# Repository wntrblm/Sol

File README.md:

# Winterbloom Sol

Winterbloom Sol is an open-source Eurorack module. You can find out more at https://wntr.dev/sol.

## License and contributing

The code here is available under the [MIT License](firmware/LICENSE), the hardware designs are available under [CC-BY-SA 4.0](hardware/LICENSE). I welcome contributors, please read the [Code of Conduct](CODE_OF_CONDUCT.md) first. :)

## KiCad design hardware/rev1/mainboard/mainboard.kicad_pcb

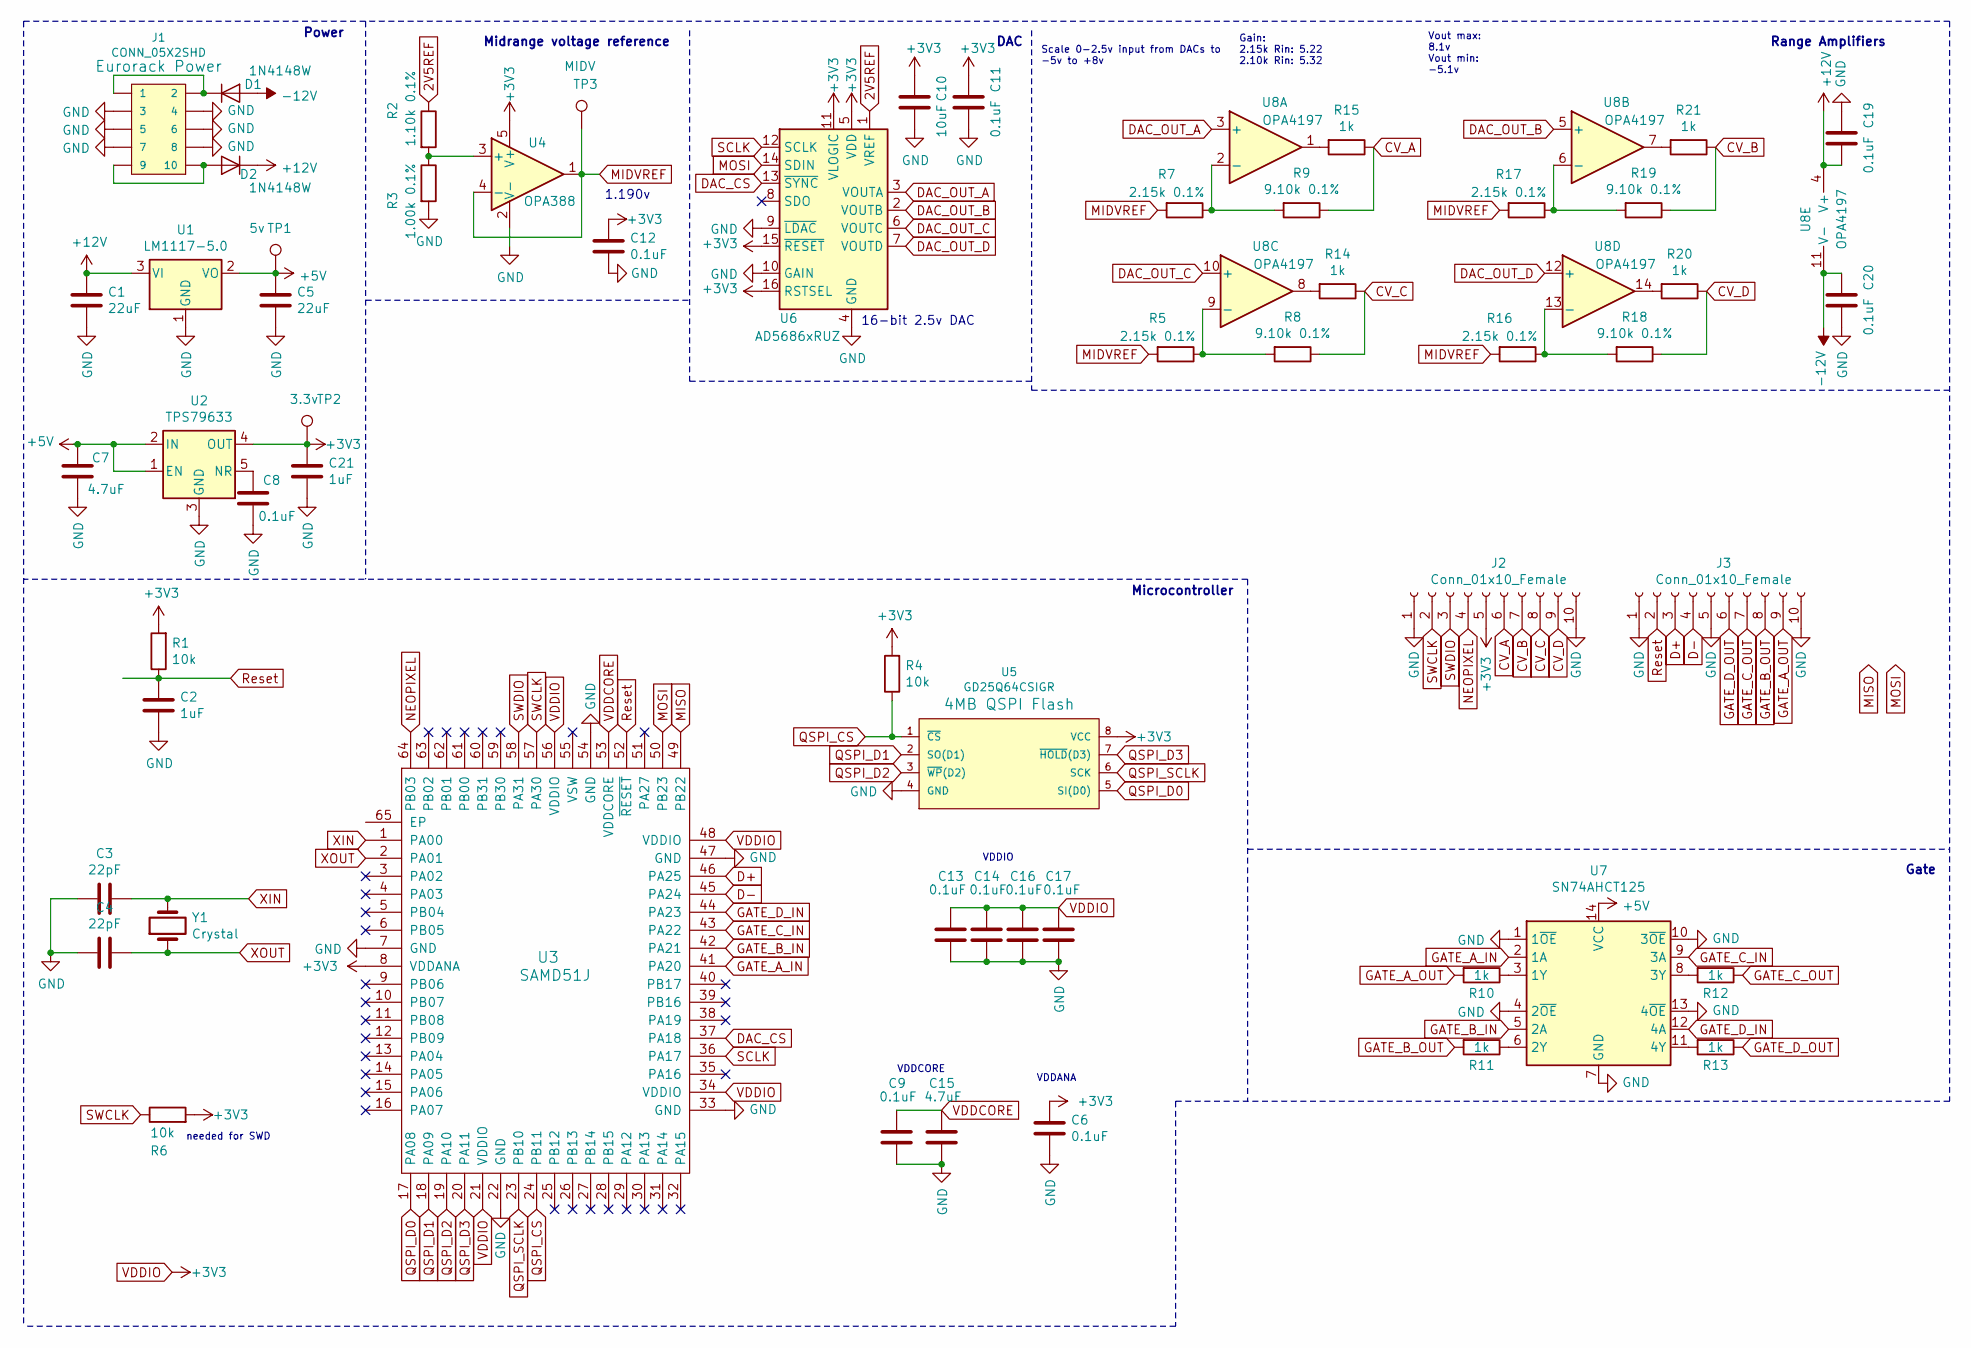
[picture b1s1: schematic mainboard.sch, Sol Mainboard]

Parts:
C1, C5: 22uF; C_0805_2012Metric_Pad1.15x1.40mm_HandSolder; mpn GRM21BR61E226ME44L
C2, C21: 1uF; C_0603_1608Metric_Pad1.05x0.95mm_HandSolder; mpn MF-CAP-0603-1uF
C3, C4: 22pF; C_0603_1608Metric_Pad1.05x0.95mm_HandSolder; mpn MF-CAP-0603-22pF
C6, C8, C9, C11, C12, C13, C14, C16, C17, C19, C20: 0.1uF; C_0603_1608Metric_Pad1.05x0.95mm_HandSolder; mpn MF-CAP-0603-0.1uF
C7, C15: 4.7uF; C_0805_2012Metric_Pad1.15x1.40mm_HandSolder; mpn GRM21BZ71E475KE15L
C10: 10uF; C_1206_3216Metric_Pad1.42x1.75mm_HandSolder; mpn MF-CAP-1206-10uF
D1, D2: 1N4148W; D_SOD-123; mpn MF-DIO-SOD123-1N4148
J1: CONN_05X2SHD; 2X5-SHROUDED; mpn 61201021621
J2, J3: Conn_01x10_Female; 1X10; mpn MF-CON-2.54mm-01x10
R1, R4, R6: 10k; R_0805_2012Metric_Pad1.15x1.40mm_HandSolder; mpn MF-RES-0805-10K
R2: 1.10k 0.1%; R_1206_3216Metric_Pad1.42x1.75mm_HandSolder; mpn ERA-8AEB112V
R3: 1.00k 0.1%; R_1206_3216Metric_Pad1.42x1.75mm_HandSolder; mpn ERA8AEB102V
R5, R7, R16, R17: 2.15k 0.1%; R_1206_3216Metric_Pad1.42x1.75mm_HandSolder; mpn ERA-8AEB2151V
R8, R9, R18, R19: 9.10k 0.1%; R_1206_3216Metric_Pad1.42x1.75mm_HandSolder; mpn ERA8AEB912V
R10, R11, R12, R13, R14, R15, R20, R21: 1k; R_0805_2012Metric_Pad1.15x1.40mm_HandSolder; mpn MF-RES-0805-1K
TP1: 5v; TestPoint_THTPad_D1.5mm_Drill0.7mm
TP2: 3.3v; TestPoint_THTPad_D1.5mm_Drill0.7mm
TP3: MIDV; TestPoint_THTPad_D1.5mm_Drill0.7mm
U1: LM1117-5.0; SOT-223-3_TabPin2; mpn LM1117IMPX-5.0/NOPB
U2: TPS79633; SOT-223-6_TabPin3; mpn TPS79633DCQR
U3: SAMD51J; TQFP-64_10x10mm_P0.5mm; mpn ATSAMD51J20A-AUT
U4: OPA388; TSOT-23-5_HandSoldering; mpn OPA388IDBVT
U5: GD25Q64CSIGR; SOIC-8; mpn GD25Q64CSIGR
U6: AD5686xRUZ; TSSOP-16_4.4x5mm_P0.65mm; mpn AD5686RBRUZ
U7: SN74AHCT125; TSSOP-14_4.4x5mm_P0.65mm; mpn SN74AHCT125QPWRQ1
U8: OPA4197; TSSOP-14_4.4x5mm_P0.65mm; mpn OPA4197IPWR
Y1: Crystal; Crystal_SMD_2012-2Pin_2.0x1.2mm_HandSoldering; mpn ABS06-32.768KHZ-1-T

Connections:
2V5REF: R2.1, U6.1 (VREF)
+5V: C5.1, C7.1, TP1.1, U1.2 (VO), U2.1 (EN), U2.2 (IN), U7.14 (VCC)
+12V: C1.1, C19.1, D2.1 (K), U1.3 (VI), U8.4 (V+)
-12V: C20.2, D1.2 (A), U8.11 (V-)
CV_A: J2.6, R9.1, R15.1
CV_B: J2.7, R19.1, R21.1
CV_C: J2.8, R8.1, R14.1
CV_D: J2.9, R18.1, R20.1
D+: J3.3, U3.46 (PA25)
D-: J3.4, U3.45 (PA24)
DAC_CS: U3.37 (PA18), U6.13 (~SYNC)
DAC_OUT_A: U6.3 (VOUTA), U8.3 (+)
DAC_OUT_B: U6.2 (VOUTB), U8.5 (+)
DAC_OUT_C: U6.6 (VOUTC), U8.10 (+)
DAC_OUT_D: U6.7 (VOUTD), U8.12 (+)
GATE_A_IN: U3.41 (PA20), U7.2 (1A)
GATE_A_OUT: J3.9, R10.2
GATE_B_IN: U3.42 (PA21), U7.5 (2A)
GATE_B_OUT: J3.8, R11.2
GATE_C_IN: U3.43 (PA22), U7.9 (3A)
GATE_C_OUT: J3.7, R12.1
GATE_D_IN: U3.44 (PA23), U7.12 (4A)
GATE_D_OUT: J3.6, R13.1
GND: C1.2, C2.2, C3.2, C4.2, C5.2, C6.2, C7.2, C8.2, C9.2, C10.2, C11.2, C12.1, C13.2, C14.2, C15.2, C16.2, C17.1, C19.2, C20.1, C21.2, J1.3, J1.4, J1.5, J1.6, J1.7, J1.8, J2.1, J2.10, J3.1, J3.5, J3.10, R3.2, U1.1 (GND), U2.3 (GND), U3.7 (GND), U3.22 (GND), U3.33 (GND), U3.47 (GND), U3.54 (GND), U4.2 (V-), U5.4 (GND), U6.4 (GND), U6.9 (~LDAC), U6.10 (GAIN), U7.1 (1~OE), U7.4 (2~OE), U7.7 (GND), U7.10 (3~OE), U7.13 (4~OE)
MIDVREF: R5.2, R7.2, R16.2, R17.2, TP3.1, U4.1, U4.4 (-)
MISO: U3.49 (PB22)
MOSI: U3.50 (PB23), U6.14 (SDIN)
NEOPIXEL: J2.4, U3.64 (PB03)
unnamed: C8.1, U2.5 (NR)
unnamed: D1.1 (K), J1.1, J1.2
unnamed: D2.2 (A), J1.9, J1.10
unnamed: R2.2, R3.1, U4.3 (+)
unnamed: R5.1, R8.2, U8.9 (-)
unnamed: R7.1, R9.2, U8.2 (-)
unnamed: R10.1, U7.3 (1Y)
unnamed: R11.1, U7.6 (2Y)
unnamed: R12.2, U7.8 (3Y)
unnamed: R13.2, U7.11 (4Y)
unnamed: R14.2, U8.8
unnamed: R15.2, U8.1
unnamed: R16.1, R18.2, U8.13 (-)
unnamed: R17.1, R19.2, U8.6 (-)
unnamed: R20.2, U8.14
unnamed: R21.2, U8.7
QSPI_CS: R4.1, U3.24 (PB11), U5.1 (~CS~)
QSPI_D0: U3.17 (PA08), U5.5 (SI(D0))
QSPI_D1: U3.18 (PA09), U5.2 (SO(D1))
QSPI_D2: U3.19 (PA10), U5.3 (~WP~(D2))
QSPI_D3: U3.20 (PA11), U5.7 (~HOLD~(D3))
QSPI_SCLK: U3.23 (PB10), U5.6 (SCK)
Reset: C2.1, J3.2, R1.1, U3.52 (~RESET)
SCLK: U3.36 (PA17), U6.12 (SCLK)
SWCLK: J2.2, R6.1, U3.57 (PA30)
SWDIO: J2.3, U3.58 (PA31)
VDDCORE: C9.1, C15.1, U3.53 (VDDCORE)
VDDIO: C6.1, C10.1, C11.1, C12.2, C13.1, C14.1, C16.1, C17.2, C21.1, J2.5, R1.2, R4.2, R6.2, TP2.1, U2.4 (OUT), U3.8 (VDDANA), U3.21 (VDDIO), U3.34 (VDDIO), U3.48 (VDDIO), U3.56 (VDDIO), U4.5 (V+), U5.8 (VCC), U6.5 (VDD), U6.11 (VLOGIC), U6.15 (~RESET), U6.16 (RSTSEL)
XIN: C3.1, U3.1 (PA00), Y1.2
XOUT: C4.1, U3.2 (PA01), Y1.1

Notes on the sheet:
Power
Microcontroller
16-bit 2.5v DAC
Midrange voltage reference
1.190v
DAC
Gate
Scale 0-2.5v input from DACs to -5v to +8v
Range Amplifiers
Gain: 2.15k Rin: 5.22 2.10k Rin: 5.32
Vout max: 8.1v Vout min: -5.1v
needed for SWD
VDDIO
VDDCORE
VDDANA

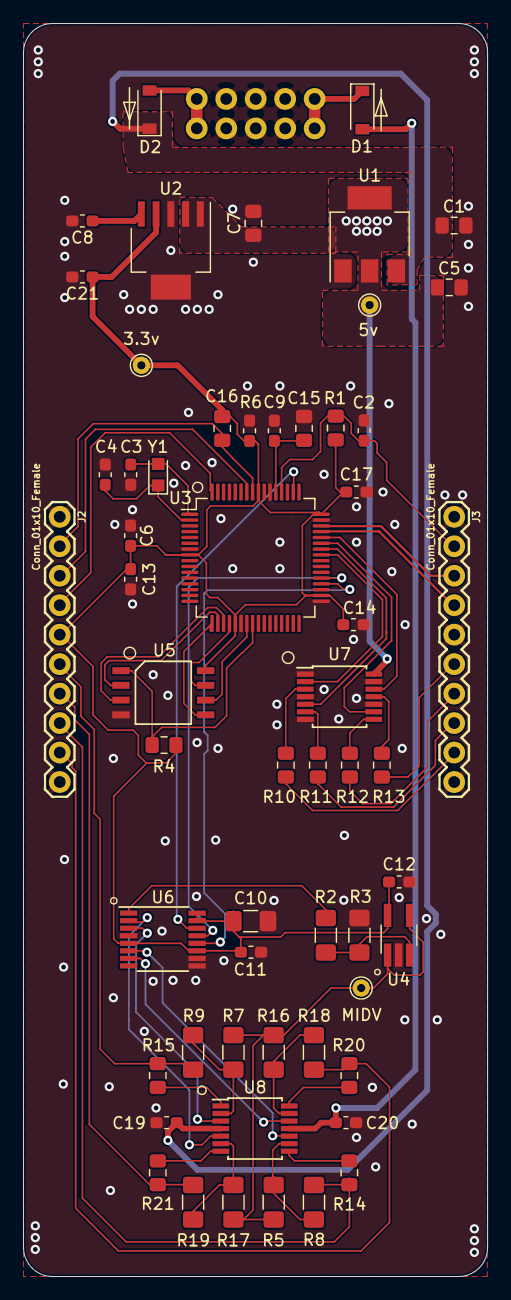
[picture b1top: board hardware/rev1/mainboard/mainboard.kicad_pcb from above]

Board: 2 copper layers, 40.0 x 108.0 mm, 58 parts (1 on the bottom side), 57 nets.

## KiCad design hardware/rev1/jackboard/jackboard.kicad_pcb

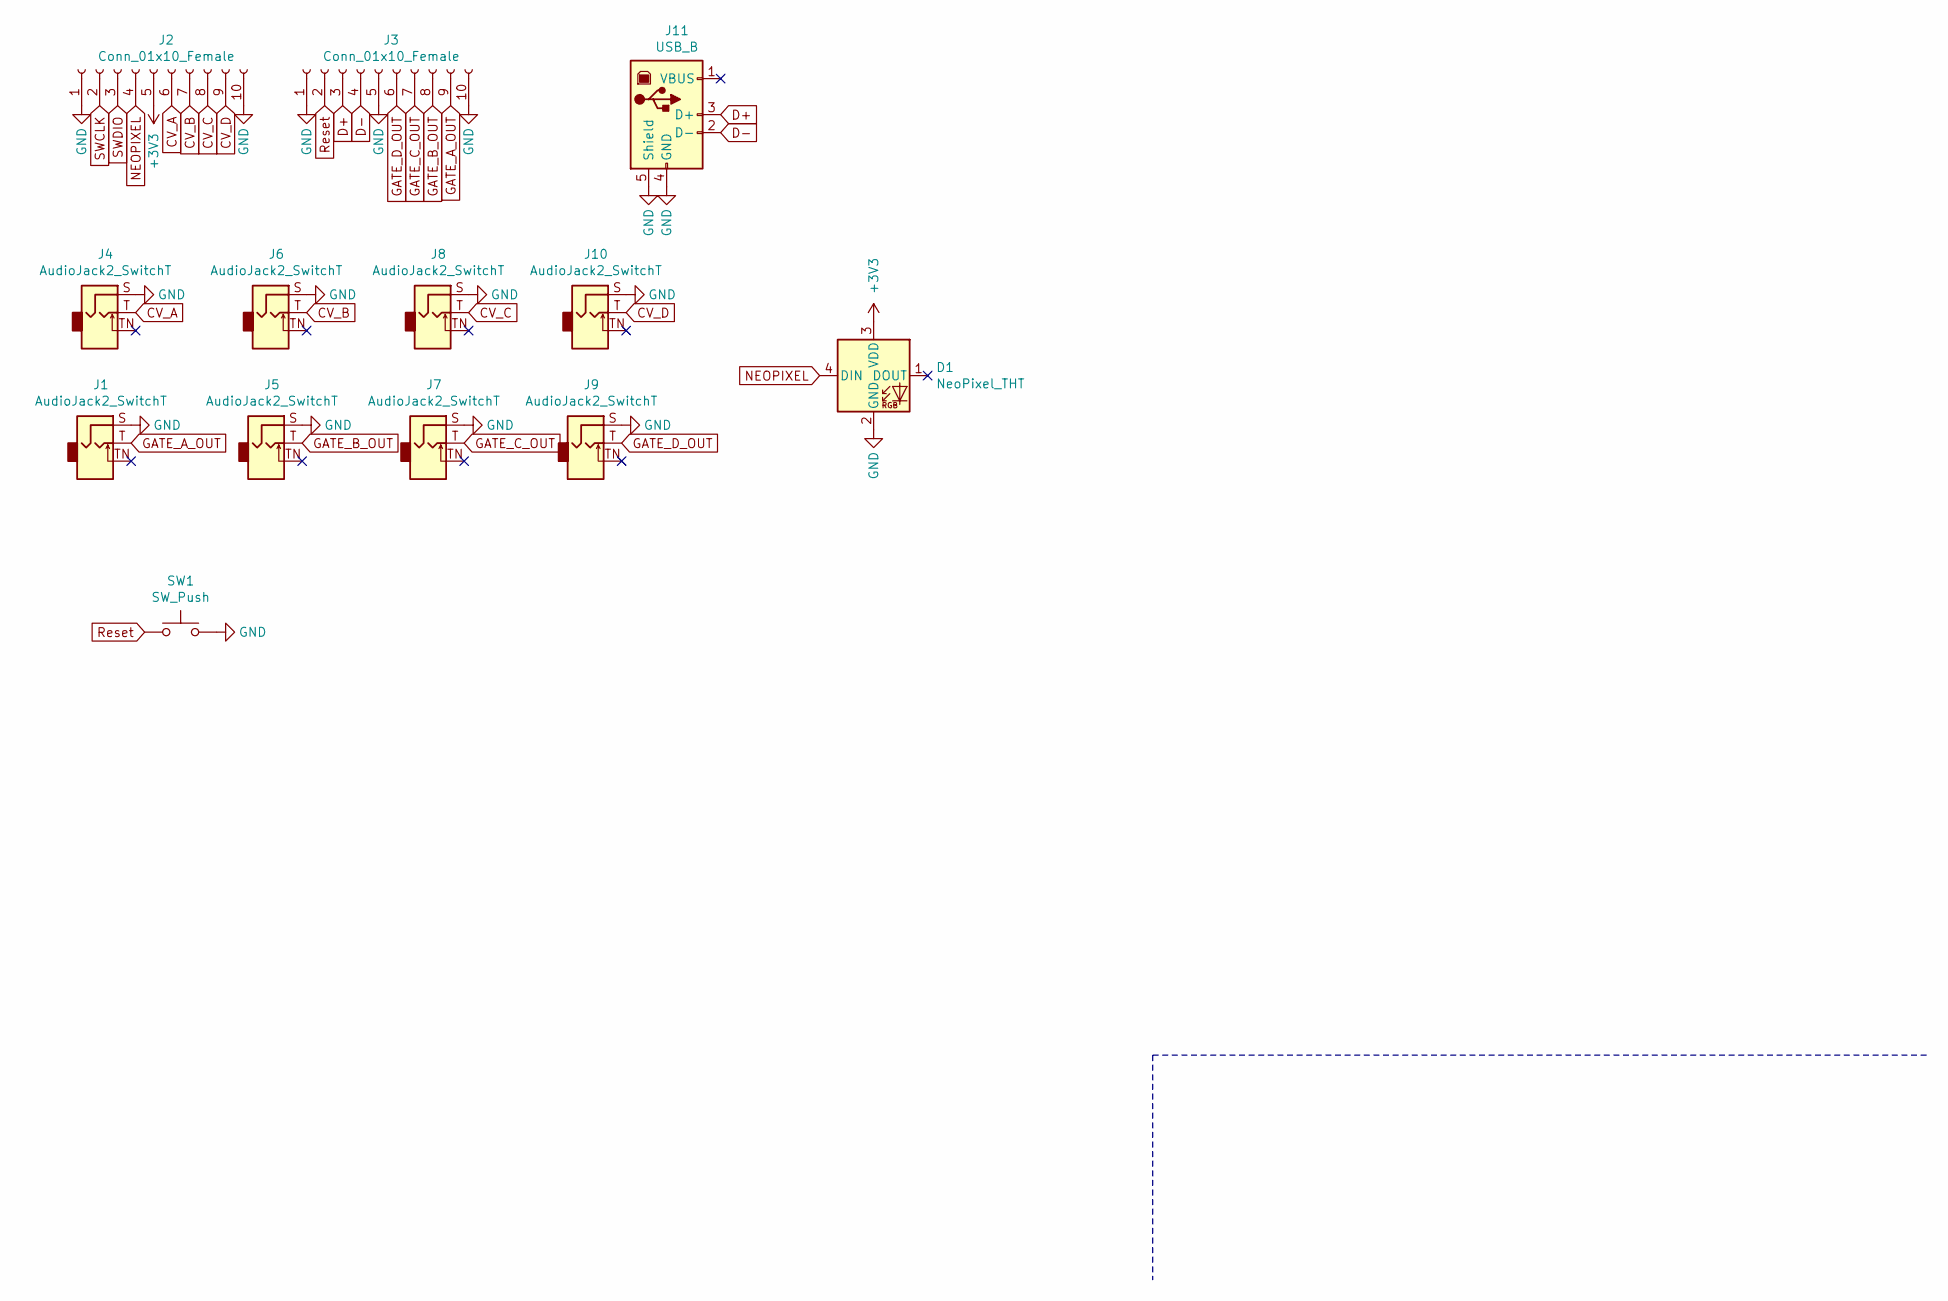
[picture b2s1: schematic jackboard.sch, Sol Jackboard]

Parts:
D1: NeoPixel_THT; LED_D5.0mm-4_RGB
J1, J4, J5, J6, J7, J8, J9, J10: AudioJack2_SwitchT; WQP-PJ301M-12_JACK
J2, J3: Conn_01x10_Female; 1X10_LOCK
J11: USB_B; USB_B_TE_5787834_Vertical
SW1: SW_Push; SW_PUSH_6mm

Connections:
+3V3: D1.3 (VDD), J2.5
CV_A: J2.6, J4.T
CV_B: J2.7, J6.T
CV_C: J2.8, J8.T
CV_D: J2.9, J10.T
D+: J3.3, J11.3 (D+)
D-: J3.4, J11.2 (D-)
GATE_A_OUT: J1.T, J3.9
GATE_B_OUT: J3.8, J5.T
GATE_C_OUT: J3.7, J7.T
GATE_D_OUT: J3.6, J9.T
GND: D1.2 (GND), J1.S, J2.1, J2.10, J3.1, J3.5, J3.10, J4.S, J5.S, J6.S, J7.S, J8.S, J9.S, J10.S, J11.4 (GND), J11.5 (Shield), SW1.2
NEOPIXEL: D1.4 (DIN), J2.4
Reset: J3.2, SW1.1
SWCLK: J2.2
SWDIO: J2.3

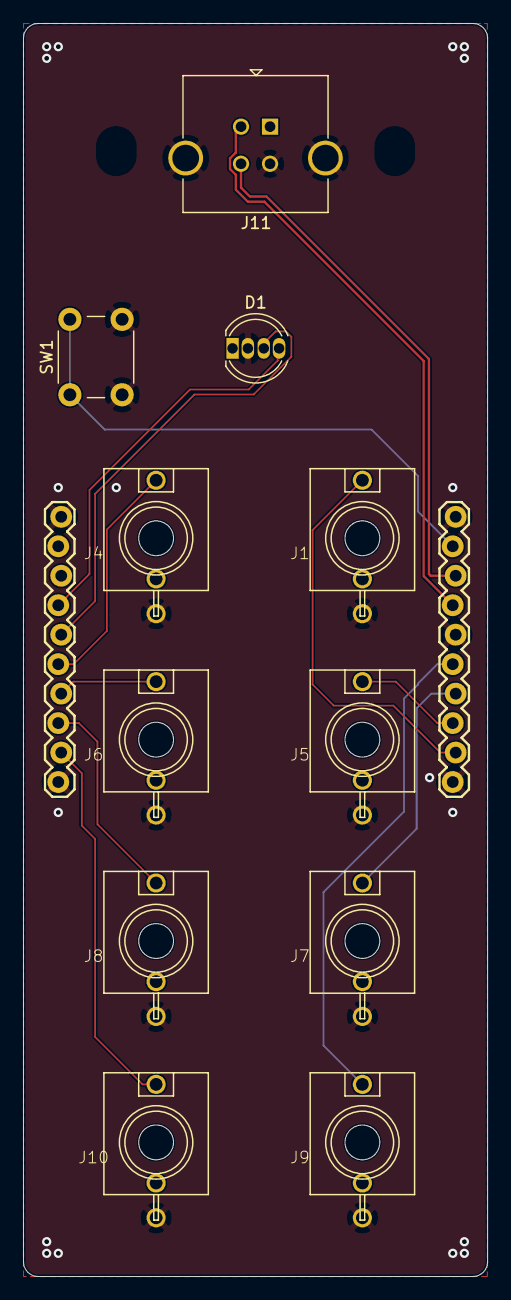
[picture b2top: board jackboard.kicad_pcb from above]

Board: 2 copper layers, 40.0 x 108.0 mm, 13 parts (0 on the bottom side), 14 nets.

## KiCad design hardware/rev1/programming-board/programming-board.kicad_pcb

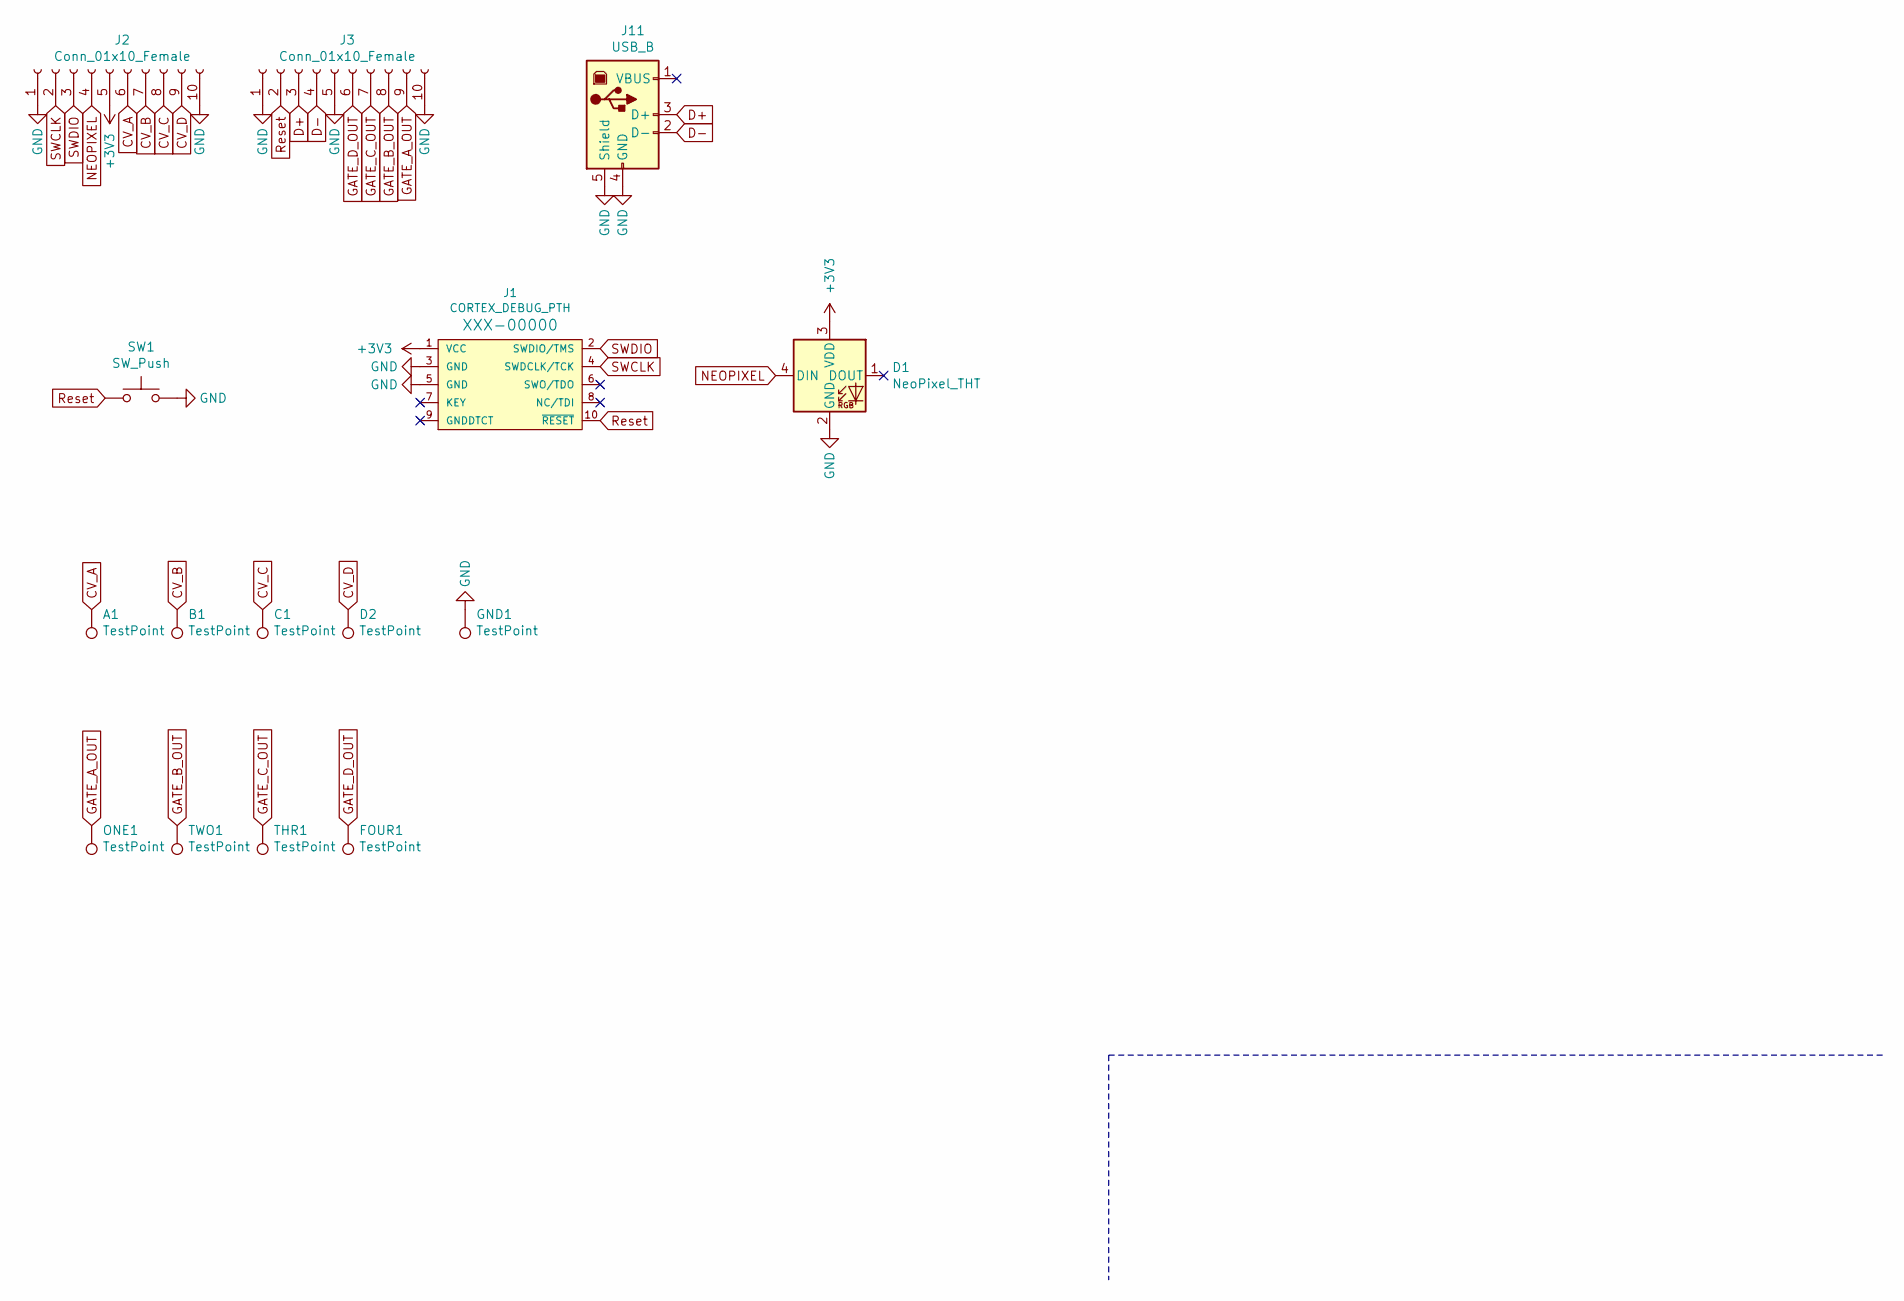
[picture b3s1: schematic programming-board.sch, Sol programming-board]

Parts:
A1: TestPoint; TestPoint_THTPad_D2.0mm_Drill1.0mm
B1: TestPoint; TestPoint_THTPad_D2.0mm_Drill1.0mm
C1: TestPoint; TestPoint_THTPad_D2.0mm_Drill1.0mm
D1: NeoPixel_THT; LED_D5.0mm-4_RGB
D2: TestPoint; TestPoint_THTPad_D2.0mm_Drill1.0mm
FOUR1: TestPoint; TestPoint_THTPad_D2.0mm_Drill1.0mm
GND1: TestPoint; TestPoint_THTPad_D2.0mm_Drill1.0mm
J1: CORTEX_DEBUG_PTH; 2X5-PTH-1.27MM
J2, J3: Conn_01x10_Female; 1X10_LOCK
J11: USB_B; USB_B_TE_5787834_Vertical
ONE1: TestPoint; TestPoint_THTPad_D2.0mm_Drill1.0mm
SW1: SW_Push; SW_PUSH_6mm
THR1: TestPoint; TestPoint_THTPad_D2.0mm_Drill1.0mm
TWO1: TestPoint; TestPoint_THTPad_D2.0mm_Drill1.0mm

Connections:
+3V3: D1.3 (VDD), J1.1 (VCC), J2.5
CV_A: A1.1, J2.6
CV_B: B1.1, J2.7
CV_C: C1.1, J2.8
CV_D: D2.1, J2.9
D+: J3.3, J11.3 (D+)
D-: J3.4, J11.2 (D-)
GATE_A_OUT: J3.9, ONE1.1
GATE_B_OUT: J3.8, TWO1.1
GATE_C_OUT: J3.7, THR1.1
GATE_D_OUT: FOUR1.1, J3.6
GND: D1.2 (GND), GND1.1, J1.3 (GND), J1.5 (GND), J2.1, J2.10, J3.1, J3.5, J3.10, J11.4 (GND), J11.5 (Shield), SW1.2
NEOPIXEL: D1.4 (DIN), J2.4
Reset: J1.10 (~RESET), J3.2, SW1.1
SWCLK: J1.4 (SWDCLK/TCK), J2.2
SWDIO: J1.2 (SWDIO/TMS), J2.3

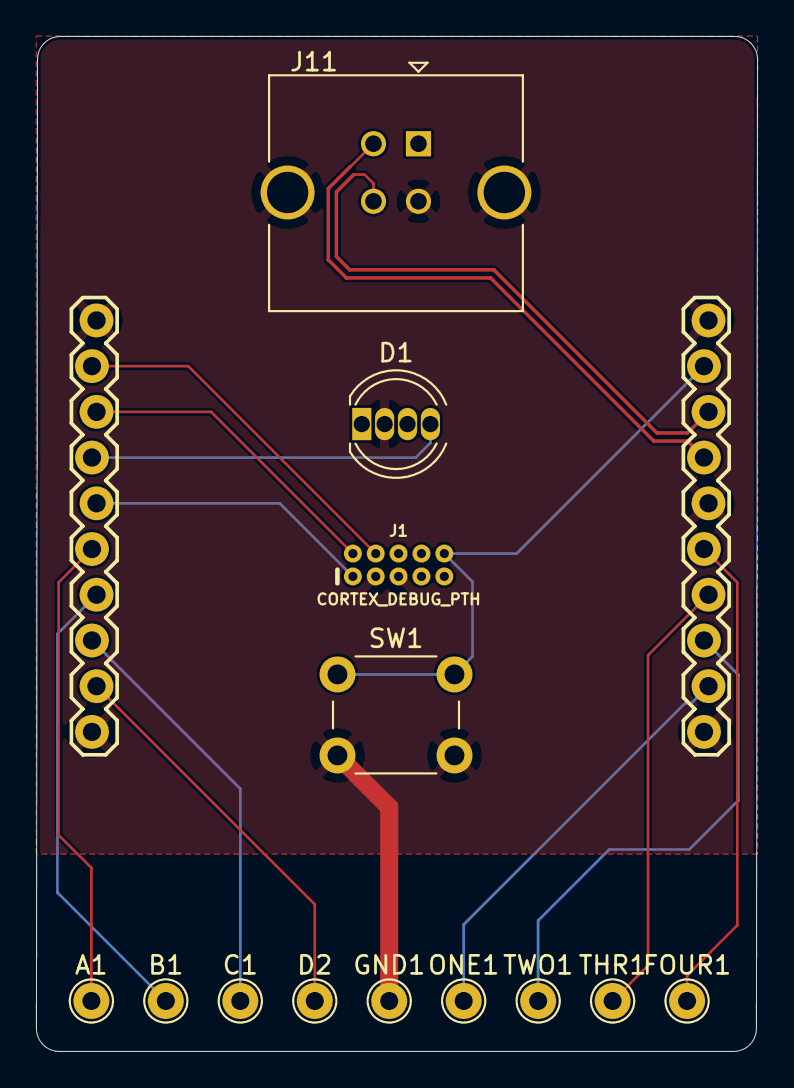
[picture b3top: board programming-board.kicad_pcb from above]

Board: 2 copper layers, 40.1 x 56.4 mm, 15 parts (0 on the bottom side), 16 nets.

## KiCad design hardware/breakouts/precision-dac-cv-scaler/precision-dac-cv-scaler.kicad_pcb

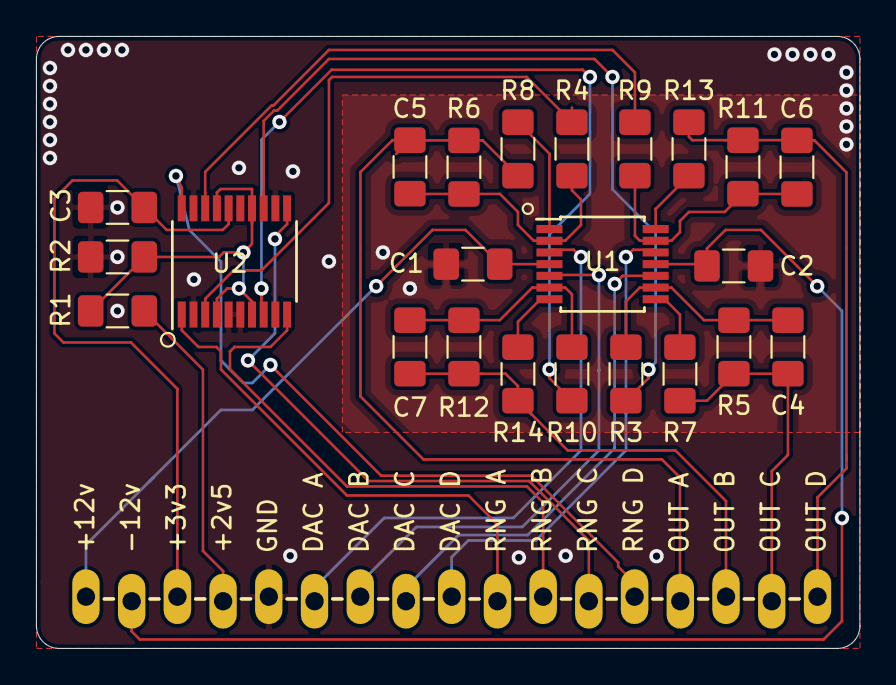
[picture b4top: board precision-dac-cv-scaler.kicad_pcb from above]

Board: 2 copper layers, 45.8 x 34.0 mm, 24 parts (0 on the bottom side), 30 nets.

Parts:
C1, C2, C3: 0.1uF; C_1206_3216Metric_Pad1.42x1.75mm_HandSolder
C4, C5, C6, C7: 22pF; C_1206_3216Metric_Pad1.42x1.75mm_HandSolder
J1: CONN_20LOCK_LONGPADS; 1X20_LOCK_LONGPADS
R1: 4.70k 0.1%; R_1206_3216Metric_Pad1.42x1.75mm_HandSolder
R2: 9.1k 0.1%; R_1206_3216Metric_Pad1.42x1.75mm_HandSolder
R3, R4, R9, R10: 2.94k 0.1%; R_1206_3216Metric_Pad1.42x1.75mm_HandSolder
R5, R6, R11, R12: 8.87k 0.1%; R_1206_3216Metric_Pad1.42x1.75mm_HandSolder
R7, R8, R13, R14: 1k 0.1%; R_1206_3216Metric_Pad1.42x1.75mm_HandSolder
U1: OPA4180; TSSOP-14_4.4x5mm_P0.65mm
U2: TMUX1134; TSSOP-20_4.4x6.5mm_P0.65mm

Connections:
+2V5: J1.4, R1.1
+3V3: C3.1, J1.3, U2.16
+12V: C1.1, J1.1, U1.4
-12V: C2.2, J1.2, U1.11
DAC_A: J1.6, U1.3
DAC_B: J1.7, U1.5
DAC_C: J1.8, U1.10
DAC_D: J1.9, U1.12
GND: C1.2, C2.1, C3.2, J1.5, R2.2, U2.2, U2.5, U2.6, U2.9, U2.12, U2.19
MID_RANGE_VREF: R1.2, R2.1, U2.4, U2.7, U2.14, U2.17
unnamed: C4.2, R3.1, R5.2, U1.9
unnamed: C5.2, R4.1, R6.2, U1.2
unnamed: C6.2, R9.1, R11.2, U1.13
unnamed: C7.2, R10.1, R12.2, U1.6
unnamed: R7.2, U1.8
unnamed: R8.2, U1.1
unnamed: R13.2, U1.14
unnamed: R14.2, U1.7
OUT_A: C5.1, J1.14, R6.1, R8.1
OUT_B: C7.1, J1.15, R12.1, R14.1
OUT_C: C4.1, J1.16, R5.1, R7.1
OUT_D: C6.1, J1.17, R11.1, R13.1
RANGE_A: J1.10, U2.1
RANGE_B: J1.11, U2.10
RANGE_C: J1.12, U2.11
RANGE_D: J1.13, U2.20
RANGE_REF_A: R4.2, U2.3
RANGE_REF_B: R10.2, U2.8
RANGE_REF_C: R3.2, U2.13
RANGE_REF_D: R9.2, U2.18

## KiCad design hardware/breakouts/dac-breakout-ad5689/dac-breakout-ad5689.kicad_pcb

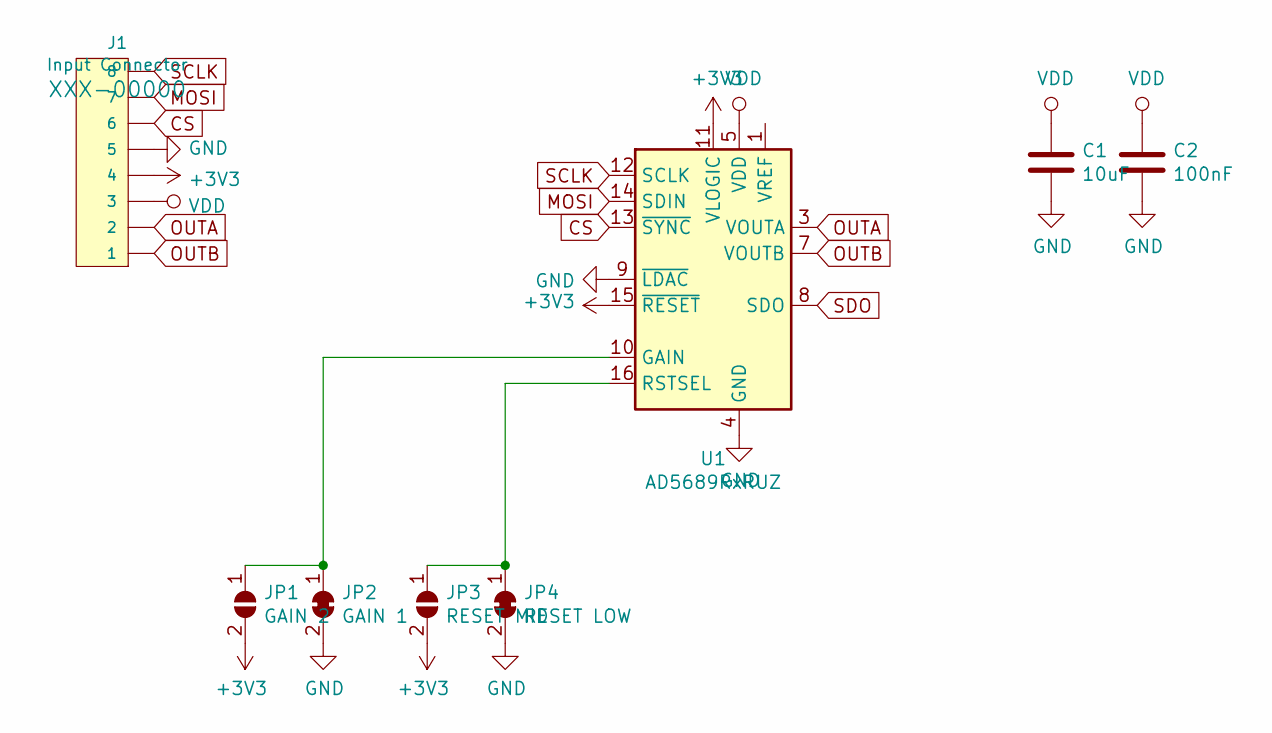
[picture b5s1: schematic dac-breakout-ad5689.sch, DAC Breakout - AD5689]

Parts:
C1: 10uF; C_1210_3225Metric_Pad1.42x2.65mm_HandSolder
C2: 100nF; C_1210_3225Metric_Pad1.42x2.65mm_HandSolder
J1: Input Connector; 1X08_LOCK_LONGPADS
JP1: GAIN 2; SolderJumper-2_P1.3mm_Open_Pad1.0x1.5mm
JP2: GAIN 1; SolderJumper-2_P1.3mm_Bridged_RoundedPad1.0x1.5mm
JP3: RESET MID; SolderJumper-2_P1.3mm_Open_Pad1.0x1.5mm
JP4: RESET LOW; SolderJumper-2_P1.3mm_Bridged_RoundedPad1.0x1.5mm
U1: AD5689RxRUZ; TSSOP-16_4.4x5mm_P0.65mm

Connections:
+3V3: J1.4, JP1.2 (B), JP3.2 (B), U1.11 (VLOGIC), U1.15 (~RESET)
CS: J1.6, U1.13 (~SYNC)
GND: C1.2, C2.2, J1.5, JP2.2 (B), JP4.2 (B), U1.4 (GND), U1.9 (~LDAC)
MOSI: J1.7, U1.14 (SDIN)
unnamed: JP1.1 (A), JP2.1 (A), U1.10 (GAIN)
unnamed: JP3.1 (A), JP4.1 (A), U1.16 (RSTSEL)
OUTA: J1.2, U1.3 (VOUTA)
OUTB: J1.1, U1.7 (VOUTB)
SCLK: J1.8, U1.12 (SCLK)
SDO: U1.8 (SDO)
VDD: C1.1, C2.1, J1.3, U1.5 (VDD)

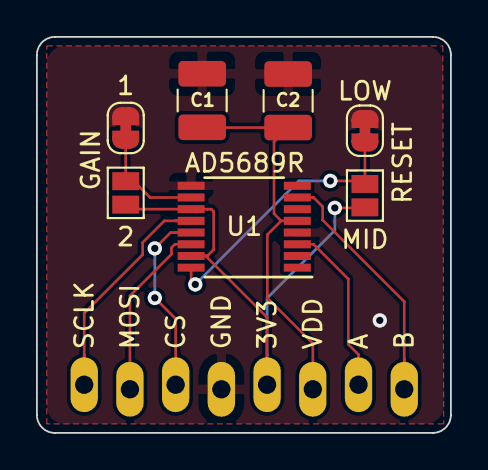
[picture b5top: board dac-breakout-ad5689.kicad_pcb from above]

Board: 2 copper layers, 23.0 x 22.0 mm, 8 parts (0 on the bottom side), 10 nets.

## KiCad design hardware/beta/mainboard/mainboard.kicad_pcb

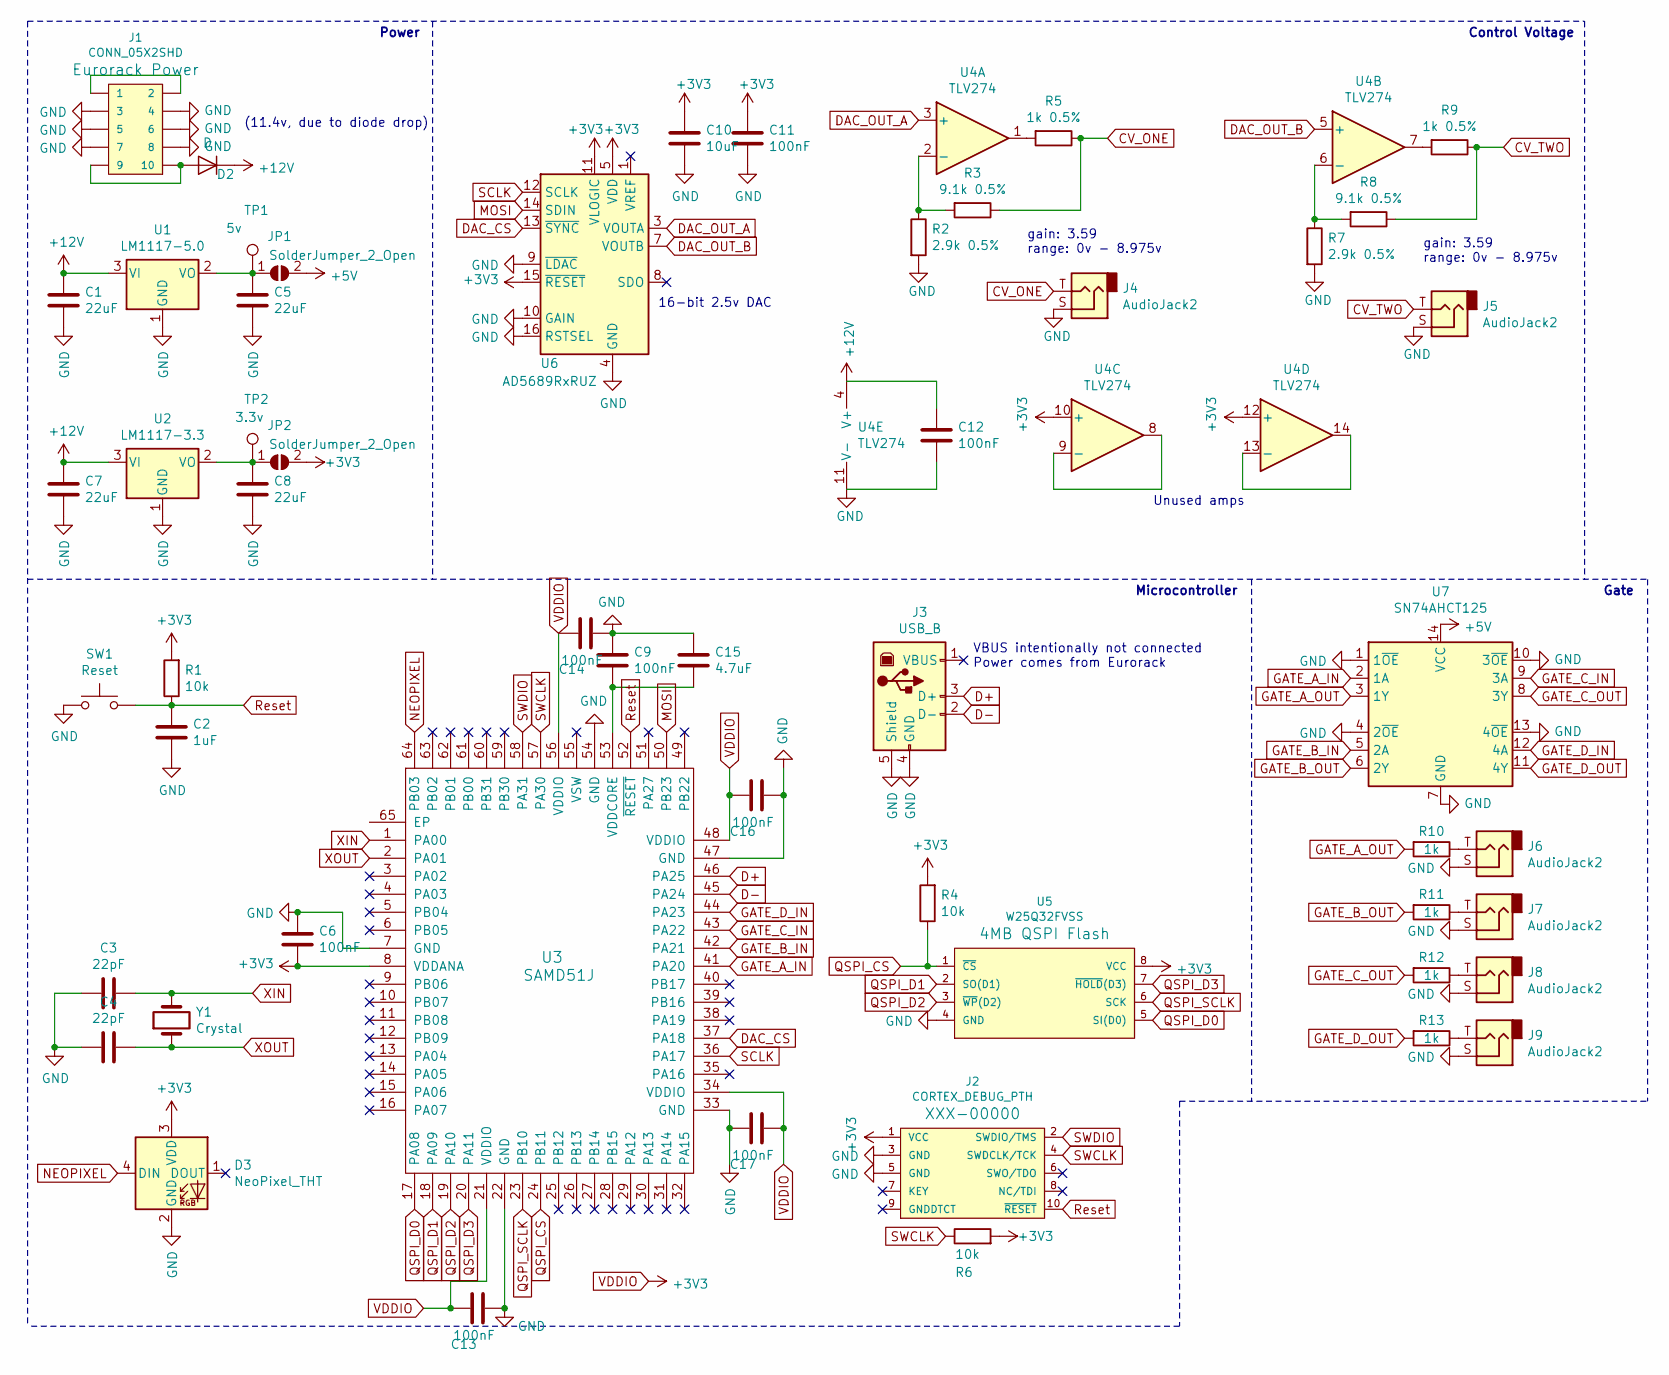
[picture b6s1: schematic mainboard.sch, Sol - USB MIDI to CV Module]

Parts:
C1, C5, C7, C8: 22uF; C_1206_3216Metric_Pad1.42x1.75mm_HandSolder
C2: 1uF; C_1206_3216Metric_Pad1.42x1.75mm_HandSolder
C3, C4: 22pF; C_1206_3216Metric_Pad1.42x1.75mm_HandSolder
C6, C9, C11, C12, C13, C14, C16, C17: 100nF; C_1206_3216Metric_Pad1.42x1.75mm_HandSolder
C10: 10uF; C_1206_3216Metric_Pad1.42x1.75mm_HandSolder
C15: 4.7uF; C_1206_3216Metric_Pad1.42x1.75mm_HandSolder
D2: D; D_0805_2012Metric_Pad1.15x1.40mm_HandSolder
D3: NeoPixel_THT; LED_D5.0mm-4_RGB
J1: CONN_05X2SHD; 2X5-SHROUDED
J2: CORTEX_DEBUG_PTH; 2X5-PTH-1.27MM
J3: USB_B; USB_B_TE_5787834_Vertical
J4, J5, J6, J7, J8, J9: AudioJack2; Jack_3.5mm_QingPu_WQP-PJ3010B
JP1, JP2: SolderJumper_2_Open; SolderJumper-2_P1.3mm_Open_RoundedPad1.0x1.5mm
R1, R4, R6: 10k; R_1206_3216Metric_Pad1.42x1.75mm_HandSolder
R2, R7: 2.9k 0.5%; R_1206_3216Metric_Pad1.42x1.75mm_HandSolder
R3, R8: 9.1k 0.5%; R_1206_3216Metric_Pad1.42x1.75mm_HandSolder
R5, R9: 1k 0.5%; R_1206_3216Metric_Pad1.42x1.75mm_HandSolder
R10, R11, R12, R13: 1k; R_1206_3216Metric_Pad1.42x1.75mm_HandSolder
SW1: Reset; TACTILE_SWITCH_PTH_6.0MM
TP1: 5v; TestPoint_THTPad_D1.5mm_Drill0.7mm
TP2: 3.3v; TestPoint_THTPad_D1.5mm_Drill0.7mm
U1: LM1117-5.0; SOT-223-3_TabPin2
U2: LM1117-3.3; SOT-223-3_TabPin2
U3: SAMD51J; TQFP-64_10x10mm_P0.5mm
U4: TLV274; TSSOP-14_4.4x5mm_P0.65mm
U5: W25Q32FVSS; SOIC-8
U6: AD5689RxRUZ; TSSOP-16_4.4x5mm_P0.65mm
U7: SN74AHCT125; TSSOP-14_4.4x5mm_P0.65mm
Y1: Crystal; Crystal_SMD_2012-2Pin_2.0x1.2mm_HandSoldering

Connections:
+5V: JP1.2 (B), U7.14 (VCC)
+12V: C1.1, C7.1, C12.2, D2.1 (K), U1.3 (VI), U2.3 (VI), U4.4 (V+)
CV_ONE: J4.T, R3.1, R5.1
CV_TWO: J5.T, R8.1, R9.1
D+: J3.3 (D+), U3.46 (PA25)
D-: J3.2 (D-), U3.45 (PA24)
DAC_CS: U3.37 (PA18), U6.13 (~SYNC)
DAC_OUT_A: U4.3 (+), U6.3 (VOUTA)
DAC_OUT_B: U4.5 (+), U6.7 (VOUTB)
GATE_A_IN: U3.41 (PA20), U7.2 (1A)
GATE_A_OUT: R10.2, U7.3 (1Y)
GATE_B_IN: U3.42 (PA21), U7.5 (2A)
GATE_B_OUT: R11.2, U7.6 (2Y)
GATE_C_IN: U3.43 (PA22), U7.9 (3A)
GATE_C_OUT: R12.2, U7.8 (3Y)
GATE_D_IN: U3.44 (PA23), U7.12 (4A)
GATE_D_OUT: R13.2, U7.11 (4Y)
GND: C1.2, C2.2, C3.2, C4.2, C5.2, C6.1, C7.2, C8.2, C9.1, C10.2, C11.2, C12.1, C13.2, C14.2, C15.1, C16.2, C17.1, D3.2 (GND), J1.3, J1.4, J1.5, J1.6, J1.7, J1.8, J2.3 (GND), J2.5 (GND), J3.4 (GND), J3.5 (Shield), J4.S, J5.S, J6.S, J7.S, J8.S, J9.S, R2.2, R7.2, SW1.1, U1.1 (GND), U2.1 (GND), U3.7 (GND), U3.22 (GND), U3.33 (GND), U3.47 (GND), U3.54 (GND), U4.11 (V-), U5.4 (GND), U6.4 (GND), U6.9 (~LDAC), U6.10 (GAIN), U6.16 (RSTSEL), U7.1 (1~OE), U7.4 (2~OE), U7.7 (GND), U7.10 (3~OE), U7.13 (4~OE)
MOSI: U3.50 (PB23), U6.14 (SDIN)
NEOPIXEL: D3.4 (DIN), U3.64 (PB03)
unnamed: C5.1, JP1.1 (A), TP1.1, U1.2 (VO)
unnamed: C8.1, JP2.1 (A), TP2.1, U2.2 (VO)
unnamed: C9.2, C15.2, U3.53 (VDDCORE)
unnamed: D2.2 (A), J1.9, J1.10
unnamed: J1.1, J1.2
unnamed: J6.T, R10.1
unnamed: J7.T, R11.1
unnamed: J8.T, R12.1
unnamed: J9.T, R13.1
unnamed: R2.1, R3.2, U4.2 (-)
unnamed: R5.2, U4.1
unnamed: R7.1, R8.2, U4.6 (-)
unnamed: R9.2, U4.7
unnamed: U4.8, U4.9 (-)
unnamed: U4.13 (-), U4.14
QSPI_CS: R4.1, U3.24 (PB11), U5.1 (~CS~)
QSPI_D0: U3.17 (PA08), U5.5 (SI(D0))
QSPI_D1: U3.18 (PA09), U5.2 (SO(D1))
QSPI_D2: U3.19 (PA10), U5.3 (~WP~(D2))
QSPI_D3: U3.20 (PA11), U5.7 (~HOLD~(D3))
QSPI_SCLK: U3.23 (PB10), U5.6 (SCK)
Reset: C2.1, J2.10 (~RESET), R1.1, SW1.2, U3.52 (~RESET)
SCLK: U3.36 (PA17), U6.12 (SCLK)
SWCLK: J2.4 (SWDCLK/TCK), R6.1, U3.57 (PA30)
SWDIO: J2.2 (SWDIO/TMS), U3.58 (PA31)
VDDIO: C6.2, C10.1, C11.1, C13.1, C14.1, C16.1, C17.2, D3.3 (VDD), J2.1 (VCC), JP2.2 (B), R1.2, R4.2, R6.2, U3.8 (VDDANA), U3.21 (VDDIO), U3.34 (VDDIO), U3.48 (VDDIO), U3.56 (VDDIO), U4.10 (+), U4.12 (+), U5.8 (VCC), U6.5 (VDD), U6.11 (VLOGIC), U6.15 (~RESET)
XIN: C3.1, U3.1 (PA00), Y1.2
XOUT: C4.1, U3.2 (PA01), Y1.1

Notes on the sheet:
gain: 3.59 range: 0v - 8.975v
Power
Microcontroller
Control Voltage
Gate
Unused amps
16-bit 2.5v DAC
VBUS intentionally not connected Power comes from Eurorack
(11.4v, due to diode drop)
